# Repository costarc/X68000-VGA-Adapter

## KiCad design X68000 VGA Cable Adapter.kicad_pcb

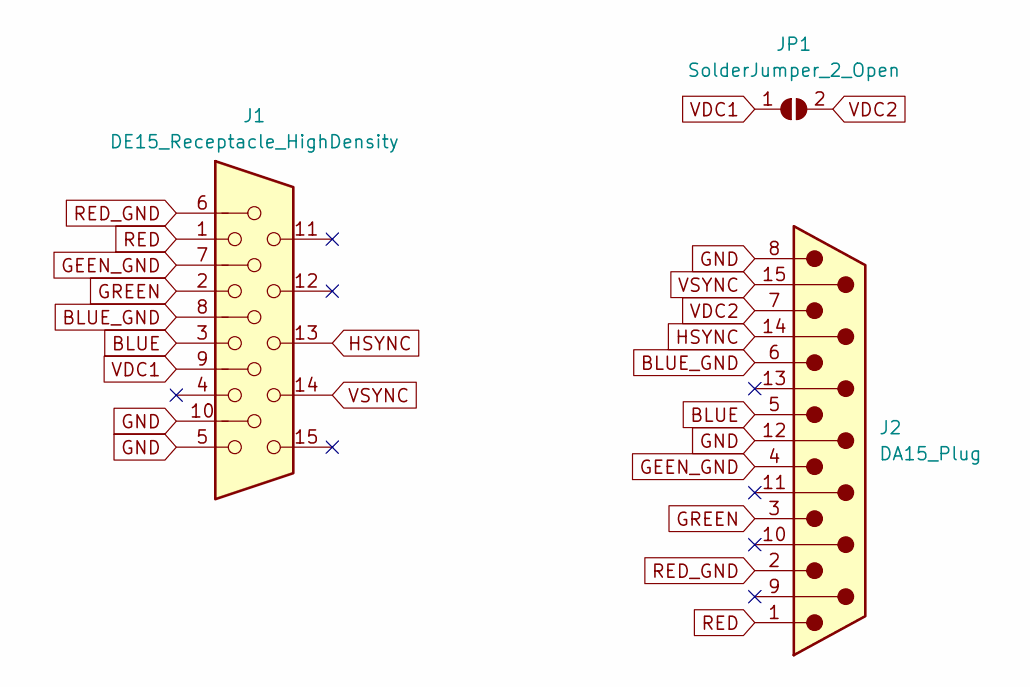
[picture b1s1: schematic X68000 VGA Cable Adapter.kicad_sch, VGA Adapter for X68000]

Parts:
J1: DE15_Receptacle_HighDensity; DSUB-15-HD_Female_Horizontal_P2.29x1.98mm_EdgePinOffset3.03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
J2: DA15_Plug; DSUB-15_Male_Horizontal_P2.77x2.84mm_EdgePinOffset7.70mm_Ho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
JP1: SolderJumper_2_Open; SolderJumper-2_P1.3mm_Open_RoundedPad1.0x1.5mm

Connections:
BLUE: J1.3, J2.5
BLUE_GND: J1.8, J2.6
GEEN_GND: J1.7, J2.4
GND: J1.5, J1.10, J2.8, J2.12
GREEN: J1.2, J2.3
HSYNC: J1.13, J2.14
RED: J1.1, J2.1
RED_GND: J1.6, J2.2
VDC1: J1.9, JP1.1 (A)
VDC2: J2.7, JP1.2 (B)
VSYNC: J1.14, J2.15

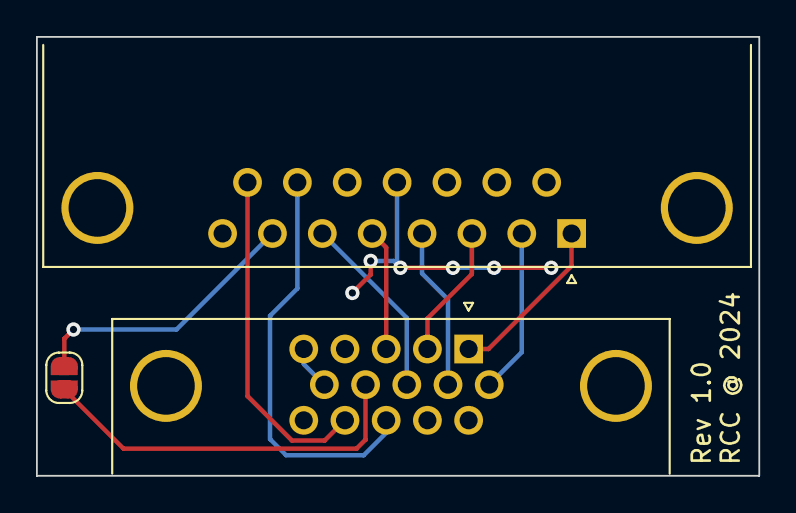
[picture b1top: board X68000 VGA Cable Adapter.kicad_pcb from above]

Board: 2 copper layers, 40.1 x 24.4 mm, 3 parts (0 on the bottom side), 11 nets.

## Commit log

2024-09-07 Rev 1.0
2024-09-07 Fabricated
